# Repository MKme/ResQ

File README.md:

# RESQ Open Source Wifi based Search and Rescue Devices
Moving super secret source to Git for sharing on Hackaday- time to give ths project away  Show it some love with a like on Hackaday IO here: https://hackaday.io/project/172090-resq-search-and-rescue-tools

Buy a DIY kit here: https://store.mkme.org/?product_cat=custom

This open source project uses beacon packet sniffing from any commercially available aircraft/drone or manned aircraft OR by a handheld YAGI antenna unit to locate people on the ground such as lost hikers, 
campers or even poachers on game preserves etc This will work even in areas where their cellphones cannot connect to any cell tower- handy.  The aircraft dtects the AP beacon from their cellular phone, records the GPS coordinates for later ground use and transmits an alert to search teams on the ground
<p align="center">
<br>
 
 <br>

<br>
<br>
🐦 <a href="https://twitter.com/mkmeorg">Twitter</a>
| 📺 <a href="https://www.youtube.com/mkmeorg">YouTube</a>
| 🌍 <a href="http://www.mkme.org">mkme.org</a><br>
Support this project and become a patron on <a href="http://mkme.org/patreon">Eric's Patreon</a>.<br>
Website, Forum and store are at http://mkme.org <br>
Chat with Me: <a href="https://discord.gg/j9S4Fgv">Discord</a></b>
</p>

# Links for more information
Hackaday Project: https://hackaday.io/project/172090-resq-open-source-search-and-rescue-tool

ResQ Tool Forum Thread For Discussion with Eric - http://mkme.org/forum/viewtopic.php?f=28&t=1130

# FULL video tutorials:

### Full playlist (all related videos/tutorials):

https://www.youtube.com/playlist?list=PLxyM2a_cfnzifVreG8aKurH-9nNYl8QLr

# Main Overview:

# System Overview 

# Kanban Board- Current Status of ResQ

#  Bill of Materials 

This list is shortened for brevity - Full BOM in excel doc in BOM folder

|     Component    | Source  |
| ---------- |----------------|
|D1 Mini Pro | https://amzn.to/2ZQArbl
|Custom PCB |  https://store.mkme.org/?product_cat=custom
|D1 Mini With antenna included| https://amzn.to/2ZNQEy1
|SD Card Reader| https://amzn.to/2XPDv6B
|0.96" OLED Display| https://amzn.to/3cCHvvj
|2.4 GHz Yagi Antenna| https://amzn.to/3gwLso9
|BN220 GPS| https://amzn.to/2ZPXUJH
|SMA adapter| https://amzn.to/3ezOpT8
|LORA Modules| https://amzn.to/2zB61ze
|18650 LiOn cells | https://amzn.to/2ZSoMsz

# Wiring 
See schematic and PCB gerber files for detailed view but this is the summary

### SPI SD Card to WEMOS D1  Wiring
| Pin On SD Reader | Pin on D1  |
| ---------- |----------------|
| SCK  | D5 |
| MISO| D6 |
| MOSI  | D7 |
| CS  | D8  |
|GND   | GND |
|VCC  | 3.3V ONLY!  |

### 0.96" OLED to WEMOS D1 
| Pin On OLED | Pin on D1  |
| ---------- |----------------|
| SDA  | D2 |
| SCL| D1 |
|GND   | GND |
|VCC  | 3.3V or 5V (depends on display)  |

### BN220 GPS Module
| Pin On GPS | Pin on Wemos D1  |
| ---------- |----------------|
| TX | 4 (2 in Arduino code) |
| RX | 3 (0 in Arduino code) |
|GND   | GND |
|VCC  | 3.3V |

# Enclosure/CAD Files Notes
- V1.4 Air unit case is first compatible enclusure for V1.1 PCBs/Gerbers as manufactured/supplied
- All boards and enclusures will follow version 1.XX will be compatible with all 1.XX PCBs and onward to 2.xx etc
- This project is my first made with Fusion 360 
- This was made from the awesome Adafruit Tutorial here (Thanks Noe!) https://www.youtube.com/watch?v=VVmOtM60VWw
- The box is fully parametric in Fusion so you can easily modify it as your needs/expansion or future changes to this project- HANDY!

# PCB Notes
## V1.1 
First to be manufactured (PCBWay)
- OLED is powered by 5V not 3.3V (just note in case yours is not 5V tolerant)
- OLED Wiring startes with VCC on the end then GND- Apparently almost every other OLED in the world outside my shop starts with GND then VCC
- OLED can be wired backwards as above point and burn your fingers....twice.... but still works after.... sigh....

## V2.1 
Project files done in KiCAD
- OLED is now powered 3.3V not 5V
- OLED VCC and Grnd reversed to accomodate the much more common pin layout 
-Pullup resistor added for SPI line
- Spare Signal wires now routed and dont need bodge wires if used
- Serial lines broken out for teletry transmission via LORA radio (or other UART radio module)

# Camera Expansion Module

ResQ Camera expansion module automatically captures images when target is aquired. This uses an ESP32 with camera
module. With the single GPIO I use this as an interrupt driven signal to wake the ESP from deep-sleep then begin capturing images to the SD card

The images can be used to correlate with the satellite imagery or existing aircraft FPV DVR footage.  It may be handy to have standalone images to quikly review any target detected. 

The code and enclosure files are now posted to this repo for all to use. Refer to the assembly manual for details. 

# ResQ Sentry

Sentry is a ResQ variant which includes the existing hardware plus the camera module inside a case which then becomes a stationary camera for monitoring human traffic in any area. Any time a new cell phone MAC address is detected- the camera module is triggered and captures still images of the area. 

This can be used in game preserves to catch poachers, private property surveillance, restricted areas, and many more! 

The GPS is still used to allow for accurate date/time stamps without the need for adding a real time clock. Time function will work without clear line of site to any satellites (it works indoors just fine).

2 different enclosures are provided:

- 	3D printable .stl version
-  Laser cut version (.svg files)

1. Install the ResQ hardware along with the camera in to the Sentry enclosure (camera through front hole)

2. Power the Sentry with an appropriate battery supply (5VDC to the ResQ) 

3. Add an appropriate solar charging system if desired (I bought this panel for $21 CAD) https://amzn.to/3hOA5qX

# Reviewing a Search Result Data Recording

All data is stored to the SD card while the unit is powered on. Perform your search then afterward- remove the SD card and download the contents to your PC. The file is datalog.txt 

You can manually review the hits and plot them one by one in Google Maps or your preffered map software or you can do them all at once: 

1. Download the datalog.txt file, 

2. Rename from datalog.txt to datalog.csv

3. Open in excel - Add a row above the data and within that row add the text LAT, LONG and MAC  above the corresponding columns for each (this will tell Google what each column is)

4. Delete all other columns as we wont need those

5. Upload to Google maps as done here https://www.youtube.com/watch?v=SLMzhOoA29M  NOTE: Google seems to limit the plots to 2000 entries so ensure your CSV file only has less than 2000 lines. 

Now You can then see all the MAC addresses plotted on a map- HANDY! 

# Reference & Press Coverage
Hackaday Article: https://hackaday.com/2020/08/12/resq-hunts-for-lost-hikers-from-the-air/

Hackaday Prize 2020 Finalist status: https://hackaday.io/contest/171491-supplyframe-designlab-2020-hackaday-prize/log/183401-2020-hackaday-prize-finalists

Hackster I.O Article: https://www.hackster.io/news/resq-aims-to-help-find-lost-hikers-by-capturing-wifi-beacon-frames-6608e10e4b22

Adafruit Article: https://blog.adafruit.com/2020/08/17/resq-hunts-for-lost-hikers-from-the-airdrone-droneday/

More videos and information at http://youtube.com/mkmeorg or http://www.mkme.org
Support this project and become a patron on <a href="http://mkme.org/patreon">Eric's Patreon</a>.<br>
Website, Forum and store are at http://mkme.org <br>
Chat with Me: <a href="https://discord.gg/j9S4Fgv">Discord</a></b>

### ResQ Components/build:

D1 mini Pro External Antenna (you need to mod the board for the external to work)  https://youtu.be/hXRcJXMjlyg

SD Card Use: https://youtu.be/y-P627KBLBw
SD Card interface: http://mkme.org/forum/viewtopic.php?f=14&t=1126&p=1430#p1430

### Drone/Aircraft Builds and Tuning:

Nano Talon Build Pt 1 https://youtu.be/BveRkukH6Sg

Nano Talon Build Pt 2 https://youtu.be/9segL9kFlmg

Nano Talon Build Pt 3 https://youtu.be/56KqzPDGRqc

Nano Talon Build Pt 4 https://youtu.be/-qZ3yurwyJo

Adding 3DR telemetry radio to the Nano Talon for autonymous flight control https://youtu.be/XCQz9AeE2qA

Making a DIY 18650 2S1P battery pack for >1hr duration flight missions https://youtu.be/XwAqgR_XsYw

### Attribution

This work is licensed under a Creative Commons Attribution-NonCommercial 4.0 International License.
https://creativecommons.org/licenses/by-nc/4.0/
See notes.h and comments in main code for detailed lineage/license info

Credit M. Ray Burnette for publication as WiFi Sniffer 20161013 (MIT) 
Source https://www.hackster.io/rayburne/esp8266-mini-sniff-f6b93a  
Ray's example helped this whole project by providing a base to work and expand from.  Ray your code caused me to pull my hair out and jump for joy many many nights. You rock. I apologise for the current mess that once resembled some of your code :) 

Credit to Andreas Spiess for inspiring all of us to use ESP8266 boards more in our projects (Andreas=father of all ESP projects) : https://www.youtube.com/channel/UCu7_D0o48KbfhpEohoP7YSQ

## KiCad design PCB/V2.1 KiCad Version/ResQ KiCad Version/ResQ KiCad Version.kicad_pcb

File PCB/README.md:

# PCB and Schematics Guide 

### Welcome to Erics land of Printed Circuit Boards where everyone leaves with a shiny new project board or schematic! 

Here we have a variety of selections for your ResQ build.  

# PCB History

## V1.1 
First to be manufactured (PCBWay)
- OLED is powered by 5V not 3.3V (just note in case yours is not 5V tolerant)
- OLED Wiring startes with VCC on the end then GND- Apparently almost every other OLED in the world outside my shop starts with GND then VCC
- OLED can be wired backwards as above point and burn your fingers....twice.... but still works after.... sigh....
- Extra unused I/O is broken out (you have to add jumper wires for signal if you want to add anything) but not routed- they are fully functional in V2 and beyond

## V2.1 
Project files done in KiCAD and provided here for you!
- OLED is now powered 3.3V not 5V
- OLED VCC and Grnd reversed to accomodate the much more common pin layout 
- Pullup resistor added for SPI line
- Spare Signal wires now routed and dont need bodge wires if used
- Support for external camera expansion module added
- Serial lines broken out for teletry transmission via LORA radio (or other UART radio module)
- Ordered from PCBWay Sept 6th 2020 

## V2.2

- Nothing yet and hopefully don't need it :)

## TIPS- 

-  I have the PCBs avaialble on my website here: http://store.mkme.org/product-category/custom/
-  You can also make your own PCB under $10 at PCBWay, JLCPCB, OSHPark or other board house of your choice!  Just upload the Gerbers I have provided here and you are all set!

## Notes and Handy Informationz

V1.4 Air unit case is first compatible enclusure for V1.1 PCBs/Gerbers as manufactured/supplied

All boards and enclusures will follow version 1.XX will be compatible with all 1.XX PCBs and onward to 2.xx etc

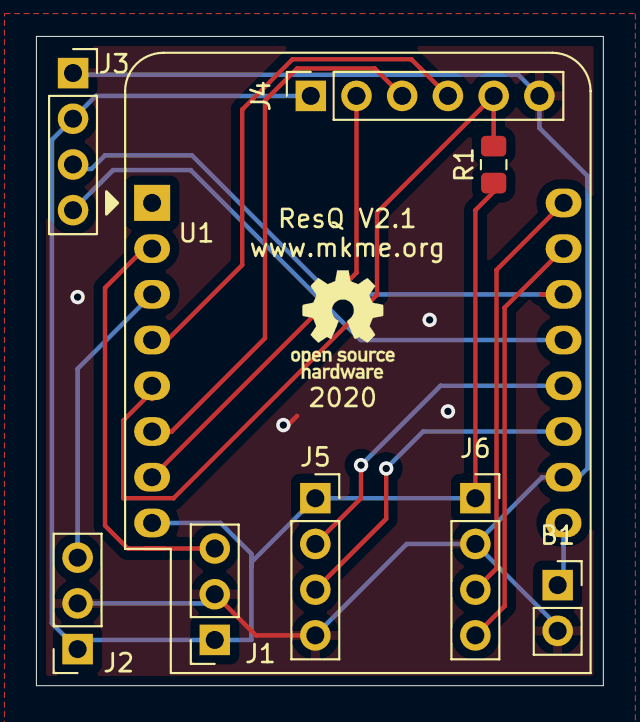
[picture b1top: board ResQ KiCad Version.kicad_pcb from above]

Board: 2 copper layers, 31.5 x 36.1 mm, 9 parts (0 on the bottom side), 15 nets.

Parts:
B1: 5V; PinSocket_1x02_P2.54mm_Vertical
J1: SP1; PinSocket_1x03_P2.54mm_Vertical
J2: Cam; PinSocket_1x03_P2.54mm_Vertical
J3: OLED; PinSocket_1x04_P2.54mm_Vertical
J4: SD Card; PinSocket_1x06_P2.54mm_Vertical
J5: GPS; PinSocket_1x04_P2.54mm_Vertical
J6: Radio; PinSocket_1x04_P2.54mm_Vertical
R1: 10k; R_0805_2012Metric_Pad1.15x1.40mm_HandSolder
U1: WeMos; WEMOS_D1_mini_light

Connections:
3V3: J1.1, J2.1, J3.2, J4.1, J5.1, J6.1, R1.1, U1.8
5V: B1.1, U1.9
A0: J1.3, U1.2
CLK: J4.4, U1.4
CS: J4.2, U1.7
D0: J2.3, U1.3
D3: J5.2, U1.12
D4: J5.3, U1.11
GND: B1.2, J1.2, J2.2, J3.1, J4.6, J5.4, J6.2, U1.10
MISO: J4.5, R1.2, U1.5
MOSI: J4.3, U1.6
RX: J6.4, U1.15
SCL: J3.3, U1.14
SDA: J3.4, U1.13
TX: J6.3, U1.16

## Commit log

2020-05-30 PicsAdded
2020-05-30 Files
2020-06-01 Code
2020-06-01 Add pcb from bak
2020-06-03 GPS Working Finally
2020-06-03 GPS Notes-Updates
2020-06-03 box added
2020-07-11 Air Unit design
2020-07-11 Interference Fit adjusted
2020-07-12 Air unit
2020-07-23 GPS Integration
2020-07-24 Update ResQ_V2.1_OLED_SD_GPS.ino
    GPS WORKING!!!
2020-07-24 Update ResQ_V2.1_OLED_SD_GPS.ino
    Fixed duplicate calls to GPS Software serial
2020-07-24 Update ResQ_V2.1_OLED_SD_GPS.ino
    Fixed SD delimitiers for logging. Still crashes periodically
2020-07-24 GPS int pics
2020-07-26 Minor updates photos & Readme
2020-07-26 Boar v1.1 complete
2020-07-26 Code Cleanup
2020-08-02 Aircraft Files Added
    Mergging from Drone Configs for anyone wishing to directly duplicate all inav settings and build
2020-08-03 pics
2020-08-04 Camera Expansion Module
2020-08-04 Cam Module Updates
2020-08-05 V3 coming
2020-08-05 Reorg and Air Unit CAD Files
2020-08-05 New Air Unit Enclosure
2020-08-06 New Air Unit box
2020-08-08 PCB Pics archive
2020-08-10 KiCad New PCB and Schematic Files
2020-08-10 KiCad Updates
2020-08-10 Updated Kicad Schem
2020-08-10 KiCAD Schematics Completed
2020-08-11 KiCAD Project Updates
2020-08-12 oled pinout reversal
2020-08-13 BOM Updates
2020-08-13 folder structure for enclosures fixed
2020-08-15 SD failure codes
    So Eric doesnt waste an hour at the park on a bad SD card anymore...
2020-08-16 Purdier schematic
2020-08-16 Purdy schematico
2020-08-16 schem
2020-08-16 Schematic purrdy
2020-08-17 Schematic Updates
2020-08-17 Telemetry radio added
2020-08-18 LORA Telemetry Reyax module
2020-08-18 links
2020-08-18 Scematic fixes
2020-08-18 PCB pics added
2020-08-21 Added Untitled Diagram.drawio
2020-08-21 Flowcharts
2020-08-22 Reorg
2020-08-22 Camera Module added
2020-08-23 Narrowed OLED Cutout
2020-08-24 Re-org for new modules and docs
2020-08-24 Schematic fixes
2020-08-26 BOM & Pics Updates
2020-08-27 Random
2020-08-27 Backup of working Libraries
2020-08-28 Laser Cut version
    Yay now anyone can make this without a 3D printer
2020-08-28 NEW Laser Cut Cases YAY
2020-08-28 Re-org for laser cut version
2020-08-28 Rename Flow Diagrams to Useful Names
2020-08-28 Sequence Overview .drawio
2020-08-28 New seq.drawio
2020-08-28 Added Main Sequence .drawio
2020-08-28 Added Main Sequence .png
2020-08-29 New laser cut svg
2020-08-29 New enclosure
2020-08-29 V1.4 Is perfect I'm DONE!
2020-08-29 2D SVG files for Air Unit Enclosure Added
2020-08-30 Ground Enclosure Design Done
2020-08-30 Ground enclosure svg
2020-08-30 Ground enclosure SVG Complete
2020-08-30 Laser Cut Enclosures
2020-08-30 Beach Test Success 8-30-2020
2020-09-02 Ref updates
2020-09-02 Removed AP SD card logging
    Serial still logged but APs were messing up the SD contents for review in Google maps
2020-09-06 Beginning PCB V2.Xxx Design
2020-09-06 PCB Version 2.1 routed
2020-09-06 PCB Updates
2020-09-06 PCB V2.1 Complete
2020-09-06 ResQ Stickers Added
2020-09-06 Gerber pictures as ordered
2020-09-07 PCB and schematic readme added
2020-09-08 Added Dimensions Only
2020-09-08 PCB V2.2 Template created
2020-09-13 Updates
    Code,Cam and sentry modes
2020-09-13 Cam Photos
2020-09-13 Cam Code Updates for white balance testing
2020-09-14 New BOM notes
2020-09-17 Cleanup
2020-09-18 PCB Pics
2020-09-19 .step source files added
2020-09-20 Cam updates
2020-09-20 Cam Enclosures
2020-09-20 ResQ Camera Integration COMPLETE!!!!
2020-09-21 Camera Module Integration COMPLETE!
    It works!
2020-09-21 Camera Module Updates
2020-09-21 Camera Module Completed
2020-09-23 ResQ Camera Updates
    Reverted whitebalance settings to Auto in main code
2020-09-23 To Be Developed .drawio
2020-09-23 Kanban.drawio
2020-09-23 Dev Plan Updates
2020-09-24 Kanban Board Current Status
2020-09-24 ResQ Sentry
2020-09-24 Sentry Mode Integration
2020-09-24 Sentry Mode Integration Done!
    Enable Sentry mode parameter in code and OLED will turn off after init to save power. Nice
2020-09-24 Sentry Mode Instructions Added
2020-09-25 Bluetooth Integration Complete!
    We can now talk to HC05 bluetooth module at 115200 baud no problem! Yay
2020-09-25 Bluetooth Integration Finalized
2020-10-04 Sentry Mode Complete
2020-10-04 User and Assembly Manual + System Design Doc
2020-10-04 Diagrams
2020-10-04 Sntry Photos with solar panel
2020-10-04 Update for CnC cutting 2D files
2020-10-14 New PCBs and Kits
2020-10-14 Kits Added
2021-01-25 Unknown
2021-04-14 Case Fonts added
2021-04-14 Fonts used added
